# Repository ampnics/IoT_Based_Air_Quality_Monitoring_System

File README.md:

# IoT_Based_Air_Quality_Monitoring_System
This project implements a real-time air quality monitoring system using IoT technology. It measures key environmental parameter like CO2 using sensors, then transmits data to a cloud platform via Wi-Fi.
A real-time air quality monitoring system that measures pollutants (CO2, NH3, NOx) and environmental parameters using IoT technology.

📋 Features
Real-time air quality monitoring using MQ135 gas sensor

OLED display for local readings

WiFi connectivity (ESP8266) for cloud data logging

Battery powered with TP4056 charging module

Compact design with CH340C USB-to-Serial interface

🛠 Hardware Components
ESP8266 - WiFi microcontroller

CH340C - USB-to-Serial converter

MT3608 - DC-DC boost converter (for 3.7V to 5V)

MQ135 - Air quality sensor (detects CO2, NH3, NOx)

AMS1117 - 3.3V voltage regulator

TP4056 - Lithium battery charging module

3.7V Li-ion Battery - Power source

0.96" OLED Display - I2C interface for local monitoring

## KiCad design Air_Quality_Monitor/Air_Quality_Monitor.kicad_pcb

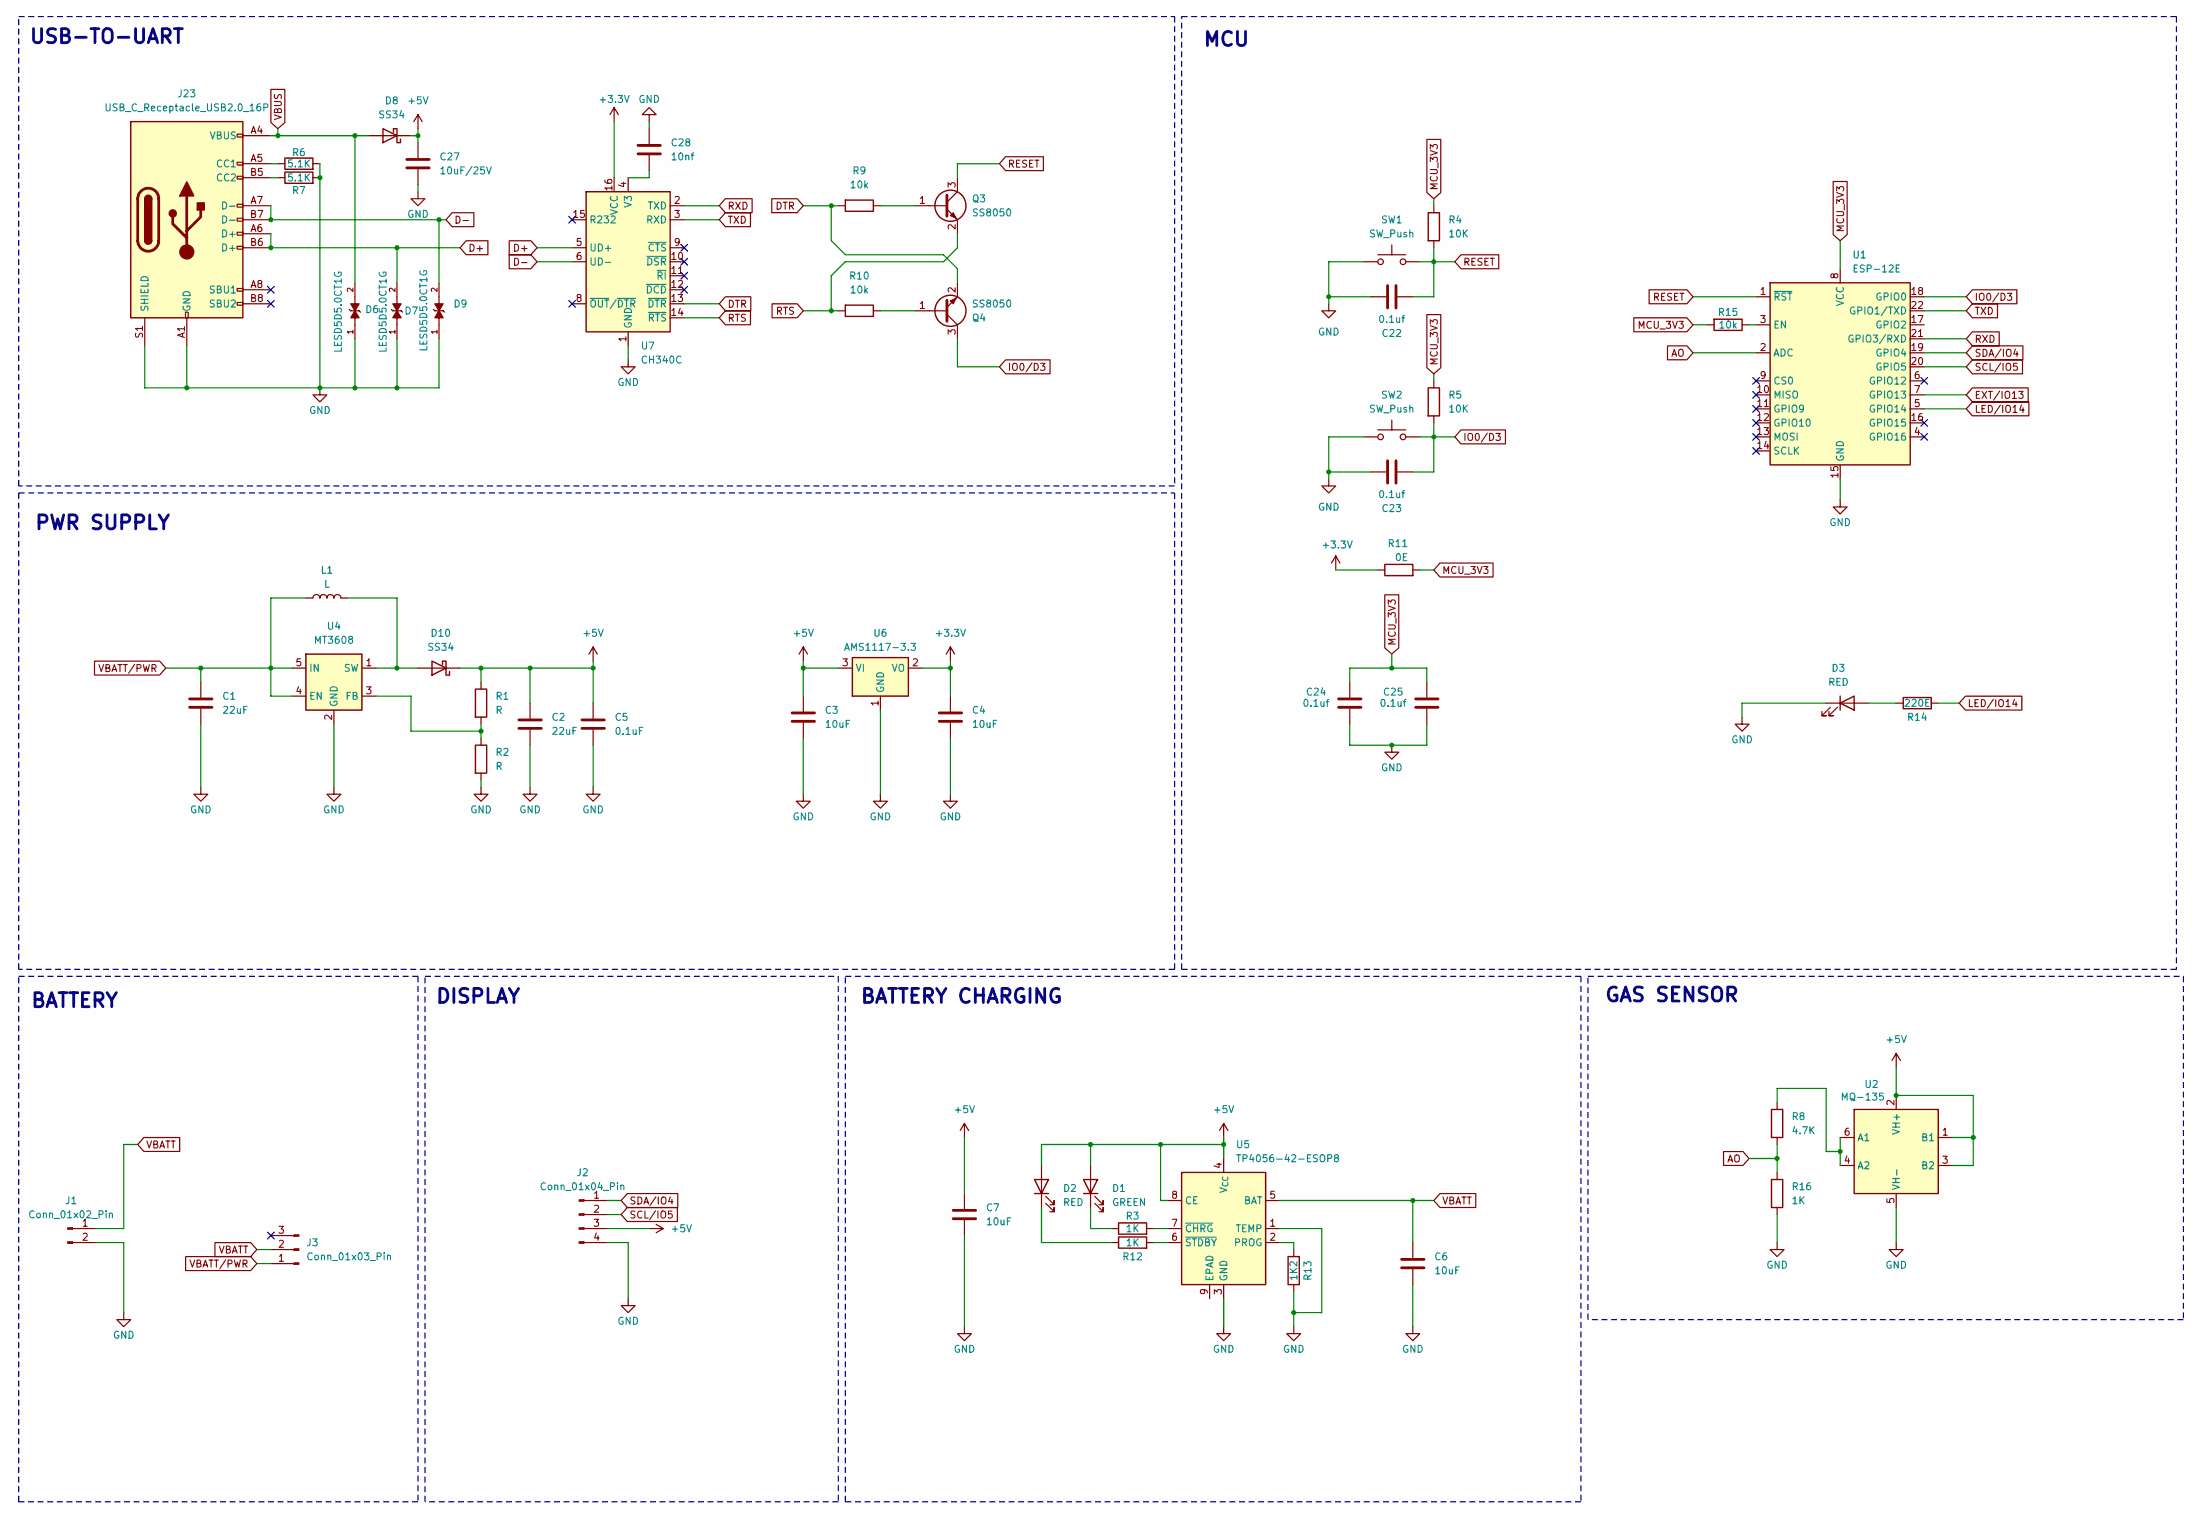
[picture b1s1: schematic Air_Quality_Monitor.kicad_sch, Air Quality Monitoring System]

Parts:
C1, C2: 22uF; C_1206_3216Metric
C3, C4, C6, C7: 10uF; C_1206_3216Metric
C5: 0.1uF; C_0603_1608Metric
C22, C23, C24, C25: 0.1uf; C_0603_1608Metric
C27: 10uF/25V; C_1206_3216Metric
C28: 10nf; C_0603_1608Metric
D1: GREEN; LED_0603_1608Metric
D2, D3: RED; LED_0603_1608Metric
D6, D7, D9: LESD5D5.0CT1G; TVS_LESD5D5.0CT1G; PARTREV O
D8, D10: SS34; D_SMA
J1: Conn_01x02_Pin; JST_PH_S2B-PH-K_1x02_P2.00mm_Horizontal
J2: Conn_01x04_Pin; PinSocket_1x04_P2.54mm_Vertical
J3: Conn_01x03_Pin; PinHeader_1x03_P2.54mm_Vertical
J23: USB_C_Receptacle_USB2.0_16P; USB_C_Receptacle_HCTL_HC-TYPE-C-16P-01A
L1: L; L_10.4x10.4_H4.8
Q3, Q4: SS8050; SOT-23
R1, R2: R; R_1206_3216Metric
R3, R12, R16: 1K; R_1206_3216Metric
R4, R5: 10K; R_1206_3216Metric
R6, R7: 5.1K; R_0603_1608Metric
R8: 4.7K; R_1206_3216Metric
R9, R10: 10k; R_0603_1608Metric
R11: 0E; R_0603_1608Metric
R13: 1K2; R_1206_3216Metric
R14: 220E; R_1206_3216Metric
R15: 10k; R_1206_3216Metric
SW1, SW2: SW_Push; SW_Push_SPST_NO_Alps_SKRK
U1: ESP-12E
U2: MQ-135; MQ-6
U4: MT3608; SOT-23-6
U5: TP4056-42-ESOP8; SOIC-8-1EP_3.9x4.9mm_P1.27mm_EP2.41x3.3mm_ThermalVias
U6: AMS1117-3.3; SOT-223-3_TabPin2
U7: CH340C; SOIC-16_3.9x9.9mm_P1.27mm

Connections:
+3.3V: C4.1, R11.1, U6.2 (VO), U7.16 (VCC)
+5V: C2.1, C3.1, C5.1, C7.1, C27.1, D1.2 (A), D2.2 (A), D8.1 (K), D10.1 (K), J2.3, R1.1, U2.1 (B1), U2.2 (VH+), U2.3 (B2), U5.4 (V_{CC}), U5.8 (CE), U6.3 (VI)
AO: R8.2, R16.1, U1.2 (ADC)
D+: D7.2, J23.A6 (D+), J23.B6 (D+), U7.5 (UD+)
D-: D9.2, J23.A7 (D-), J23.B7 (D-), U7.6 (UD-)
DTR: Q4.2 (E), R9.2, U7.13 (~DTR)
EXT/IO13: U1.7 (GPIO13)
GND: C1.2, C2.2, C3.2, C4.2, C5.2, C6.2, C7.2, C22.1, C23.1, C24.1, C25.1, C27.2, C28.1, D3.1 (K), D6.1, D7.1, D9.1, J1.2, J2.4, J23.A1 (GND), J23.A12 (GND), J23.B1 (GND), J23.B12 (GND), J23.S1 (SHIELD), R2.2, R6.2, R7.2, R13.1, R16.2, SW1.1, SW2.1, U1.15 (GND), U2.5 (VH-), U4.2 (GND), U5.1 (TEMP), U5.3 (GND), U6.1 (GND), U7.1 (GND)
IO0/D3: C23.2, Q4.3 (C), R5.2, SW2.2, U1.18 (GPIO0)
LED/IO14: R14.2, U1.5 (GPIO14)
MCU_3V3: C24.2, C25.2, R4.1, R5.1, R11.2, R15.2, U1.8 (VCC)
unnamed: D1.1 (K), R3.1
unnamed: D2.1 (K), R12.1
unnamed: D3.2 (A), R14.1
unnamed: D10.2 (A), L1.2, U4.1 (SW)
unnamed: J23.A5 (CC1), R6.1
unnamed: J23.B5 (CC2), R7.1
unnamed: Q3.1 (B), R9.1
unnamed: Q4.1 (B), R10.1
unnamed: R15.1, U1.3 (EN)
unnamed: R8.1, U2.4 (A2), U2.6 (A1)
unnamed: R1.2, R2.1, U4.3 (FB)
unnamed: R13.2, U5.2 (PROG)
unnamed: R3.2, U5.7 (~CHRG)
unnamed: R12.2, U5.6 (~STDBY)
unnamed: C28.2, U7.4 (V3)
RESET: C22.2, Q3.3 (C), R4.2, SW1.2, U1.1 (~RST)
RTS: Q3.2 (E), R10.2, U7.14 (~RTS)
RXD: U1.21 (GPIO3/RXD), U7.2 (TXD)
SCL/IO5: J2.2, U1.20 (GPIO5)
SDA/IO4: J2.1, U1.19 (GPIO4)
TXD: U1.22 (GPIO1/TXD), U7.3 (RXD)
VBATT: C6.1, J1.1, J3.2, U5.5 (BAT)
VBATT/PWR: C1.1, J3.1, L1.1, U4.4 (EN), U4.5 (IN)
VBUS: D6.2, D8.2 (A), J23.A4 (VBUS), J23.A9 (VBUS), J23.B4 (VBUS), J23.B9 (VBUS)

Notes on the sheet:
PWR SUPPLY
USB-TO-UART
DISPLAY
GAS SENSOR
BATTERY CHARGING
MCU
BATTERY

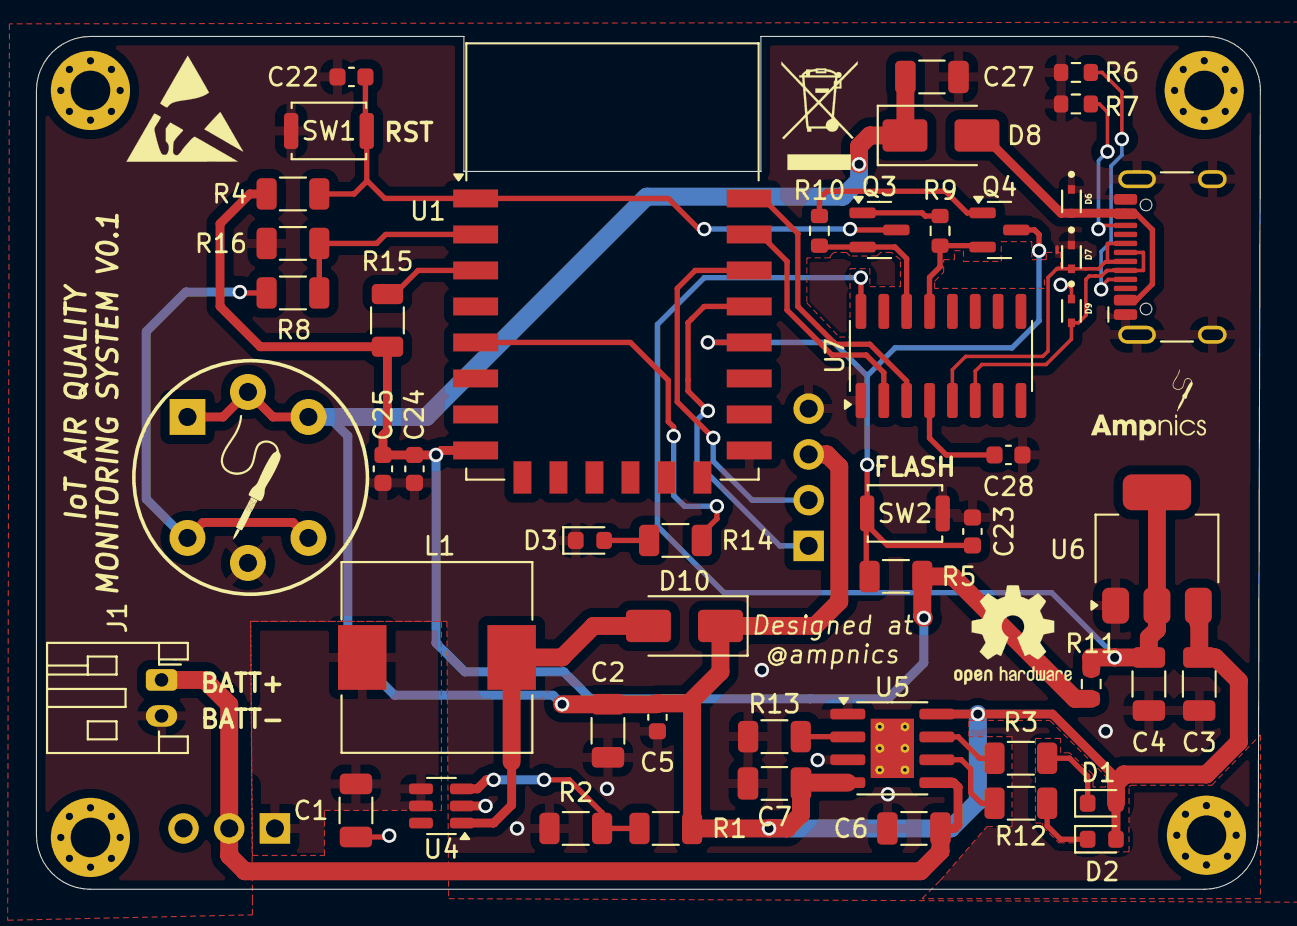
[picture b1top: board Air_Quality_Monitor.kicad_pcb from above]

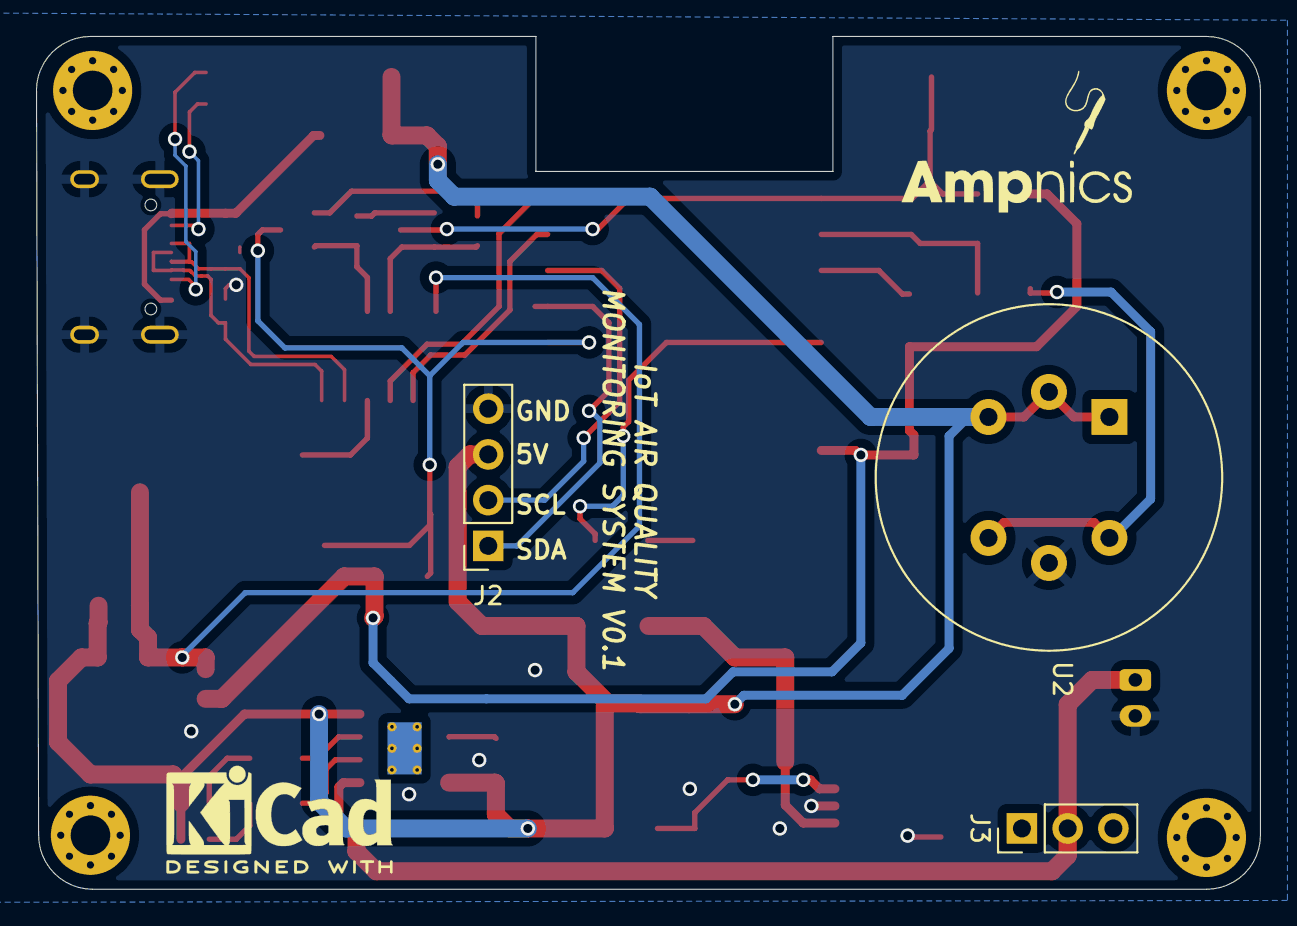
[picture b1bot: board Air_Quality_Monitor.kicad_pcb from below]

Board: 2 copper layers, 68.0 x 47.4 mm, 56 parts (3 on the bottom side), 34 nets.

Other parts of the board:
REFe: MountingHole_2.2mm_M2_Pad_Via
REFe#2, REFe#3, REFe#4: MountingHole_2.2mm_M2_Pad_Via

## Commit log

2025-03-29 README.md
